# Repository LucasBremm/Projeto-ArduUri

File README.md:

# Projeto ArduUri

## Descrição

Projeto com o objetivo de desenvolver kits robóticos reutilizando lixo eletrônico, sendo esses enviados para escolas, podendo assim desenvolver um aprendizado sobre robótica e programação, juntamente com a conscientização dos riscos ao meio ambiente ocasionados pelo descarte incorreto de componentes eletrônicos.

Atualmente nesse repositório constam:

- Uma placa de circuito que age como Controlador (baseado em Arduino) e uma ponte H para controle de motores

- Duas placas que agem separadamente como a descrita acima

- Moldes em 3D de chassis e suportes para motores, que podem ser impressos com impressora 3D

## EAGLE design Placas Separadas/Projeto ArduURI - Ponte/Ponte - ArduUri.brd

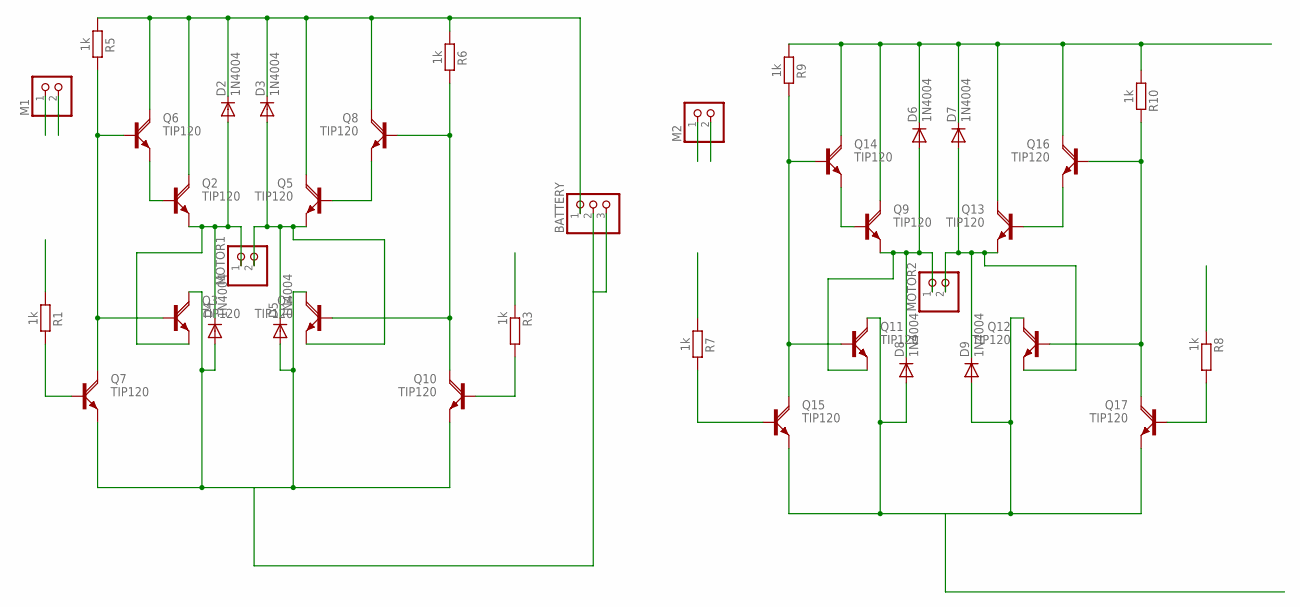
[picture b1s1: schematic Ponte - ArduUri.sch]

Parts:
BATTERY: PINHD-1X3; 1X03
D2, D3, D4, D5, D6, D7, D8, D9: 1N4004; DO41-10
M1, M2: PINHD-1X2; 1X02
MOTOR1, MOTOR2: PINHD-1X2; 1X02
Q2, Q3, Q4, Q5, Q6, Q7, Q8, Q9, Q10, Q11, Q12, Q13, Q14, Q15, Q16, Q17: TIP120; TO220AH
R1, R3, R5, R6, R7, R8, R9, R10: 1k; 0204/7

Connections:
GND: BATTERY.2, BATTERY.3, D4.A, D5.A, D8.A, D9.A, Q3.C, Q4.C, Q7.E, Q10.E, Q11.C, Q12.C, Q15.E, Q17.E
M1-A1: M1.1, R1.1
M1-B1: M1.2, R3.1
M2-A2: M2.1, R7.1
M2-B2: M2.2, R8.1
unnamed: Q5.B, Q8.E
unnamed: Q10.B, R3.2
unnamed: Q7.B, R1.2
unnamed: Q2.B, Q6.E
unnamed: Q9.B, Q14.E
unnamed: Q3.B, Q6.B, Q7.C, R5.2
unnamed: Q4.B, Q8.B, Q10.C, R6.2
unnamed: Q13.B, Q16.E
unnamed: D2.A, D4.C, MOTOR1.1, Q2.E, Q3.E
unnamed: D3.A, D5.C, MOTOR1.2, Q4.E, Q5.E
unnamed: Q17.B, R8.2
unnamed: Q15.B, R7.2
unnamed: Q11.B, Q14.B, Q15.C, R9.2
unnamed: Q12.B, Q16.B, Q17.C, R10.2
unnamed: D6.A, D8.C, MOTOR2.1, Q9.E, Q11.E
unnamed: D7.A, D9.C, MOTOR2.2, Q12.E, Q13.E
VCC-BAT: BATTERY.1, D2.C, D3.C, D6.C, D7.C, Q2.C, Q5.C, Q6.C, Q8.C, Q9.C, Q13.C, Q14.C, Q16.C, R5.1, R6.1, R9.1, R10.1

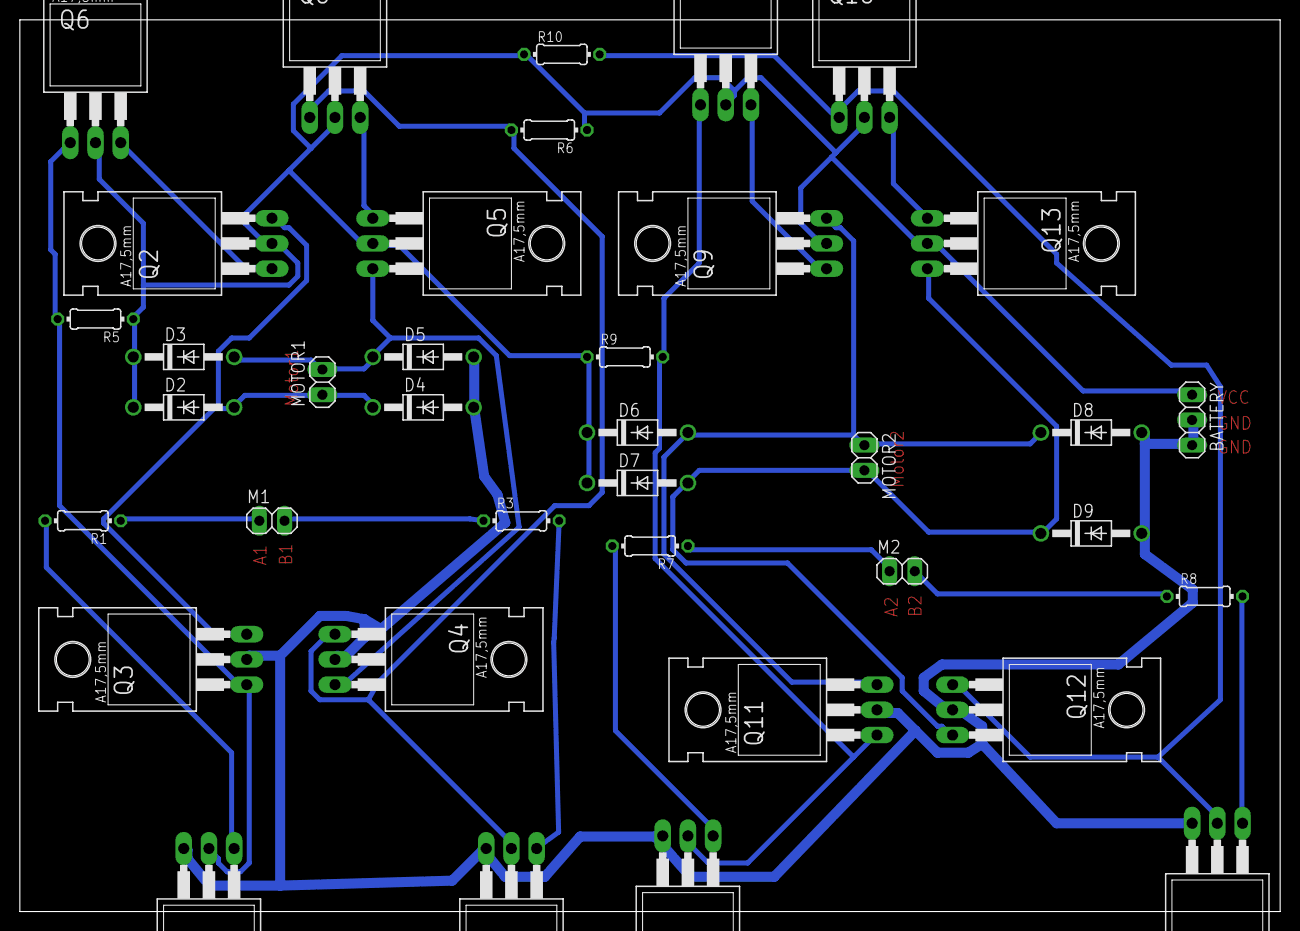
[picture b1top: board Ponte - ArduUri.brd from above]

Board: 2 copper layers, 127.0 x 89.8 mm, 37 parts (0 on the bottom side), 22 nets.

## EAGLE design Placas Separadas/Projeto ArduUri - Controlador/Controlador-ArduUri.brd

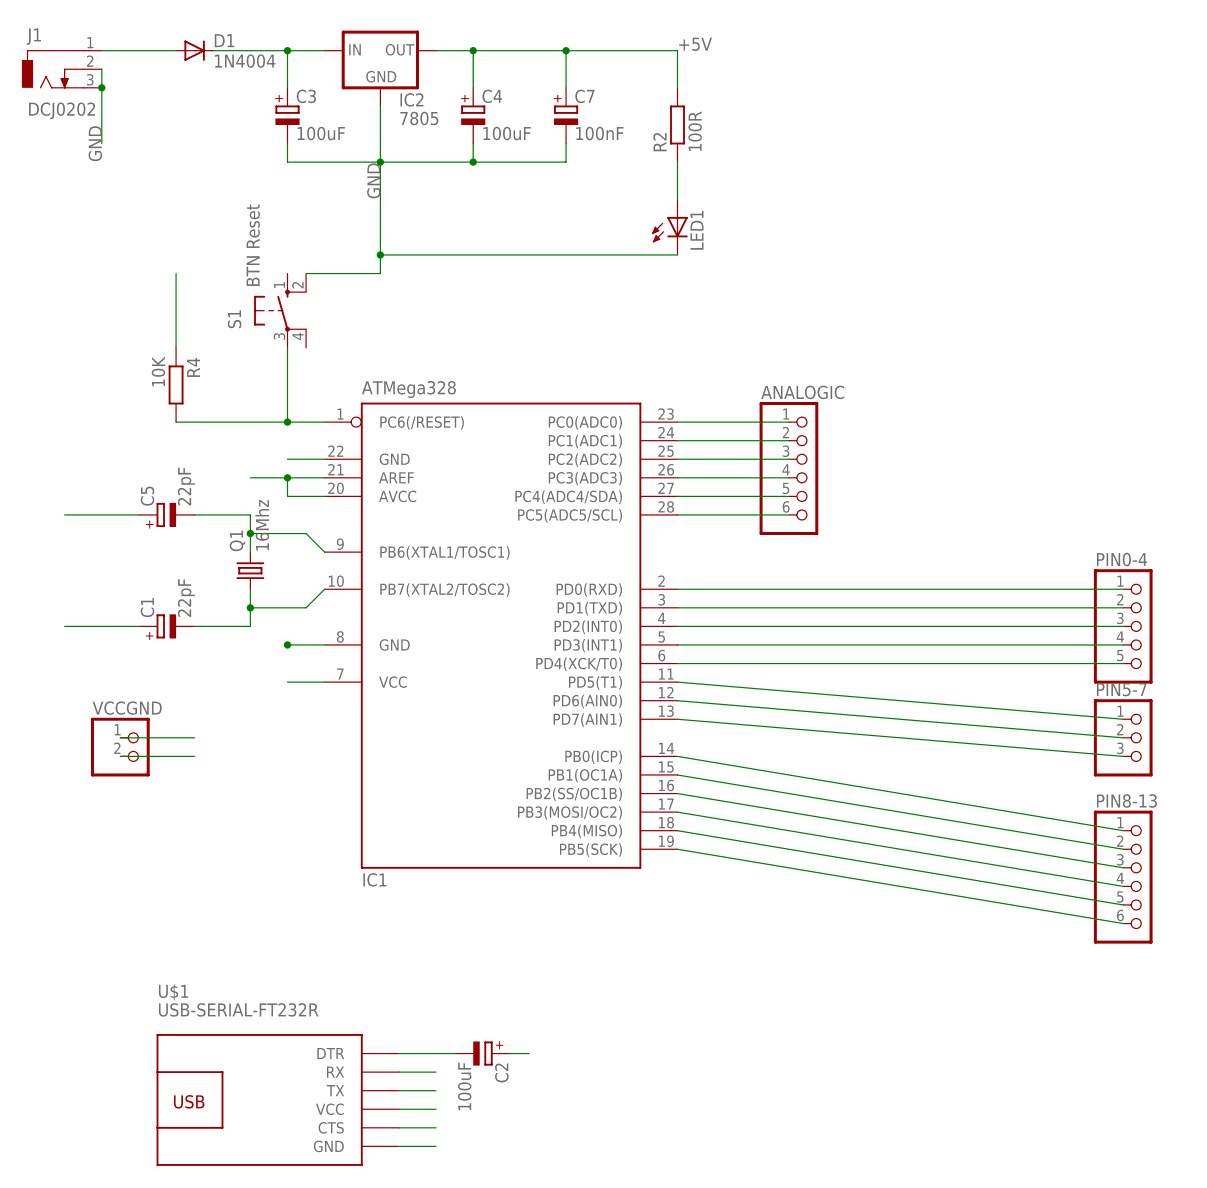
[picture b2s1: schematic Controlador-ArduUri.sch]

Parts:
ANALOGIC: PINHD-1X6; 1X06
C1, C5: 22pF; E2,5-5
C2, C3, C4: 100uF; TAP5-50
C7: 100nF; E2,5-5
D1: 1N4004; DO41-10
IC1: ATMega328; DIL28-3
IC2: 7805; 78XXL
J1: DCJ0202
LED1: LED5MM
PIN0-4: PINHD-1X5; 1X05
PIN5-7: PINHD-1X3; 1X03
PIN8-13: PINHD-1X6; 1X06
Q1: 16Mhz; HC49/S
R2: 100R; 0204/7
R4: 10K; 0204/7
S1: BTN Reset; B3F-10XX
U$1: USB-SERIAL-FT232R
VCCGND: PINHD-1X2; 1X02

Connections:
+5V: C4.+, C7.+, IC1.7 (VCC), IC1.20 (AVCC), IC1.21 (AREF), IC2.OUT, R2.2, R4.1, U$1.4 (VCC), VCCGND.1
DTR: C2.-, U$1.1 (DTR)
GND: C1.+, C3.-, C4.-, C5.+, C7.-, IC1.8 (GND), IC1.22 (GND), IC2.GND, J1.2, J1.3, LED1.K (C), S1.2 (S1), U$1.6 (GND), VCCGND.2
M1-A1: IC1.17 (PB3(MOSI/OC2)), PIN8-13.4
M1-B1: IC1.16 (PB2(SS/OC1B)), PIN8-13.3
M2-A1: IC1.12 (PD6(AIN0)), PIN5-7.2
M2-B1: IC1.11 (PD5(T1)), PIN5-7.1
unnamed: C5.-, IC1.9 (PB6(XTAL1/TOSC1)), Q1.2
unnamed: C1.-, IC1.10 (PB7(XTAL2/TOSC2)), Q1.1
unnamed: D1.A, J1.1
unnamed: C3.+, D1.C, IC2.IN
unnamed: ANALOGIC.1, IC1.23 (PC0(ADC0))
unnamed: ANALOGIC.2, IC1.24 (PC1(ADC1))
unnamed: ANALOGIC.3, IC1.25 (PC2(ADC2))
unnamed: ANALOGIC.4, IC1.26 (PC3(ADC3))
unnamed: ANALOGIC.5, IC1.27 (PC4(ADC4/SDA))
unnamed: ANALOGIC.6, IC1.28 (PC5(ADC5/SCL))
unnamed: IC1.4 (PD2(INT0)), PIN0-4.3
unnamed: IC1.5 (PD3(INT1)), PIN0-4.4
unnamed: IC1.6 (PD4(XCK/T0)), PIN0-4.5
unnamed: IC1.13 (PD7(AIN1)), PIN5-7.3
unnamed: IC1.14 (PB0(ICP)), PIN8-13.1
unnamed: IC1.15 (PB1(OC1A)), PIN8-13.2
unnamed: IC1.18 (PB4(MISO)), PIN8-13.5
unnamed: IC1.19 (PB5(SCK)), PIN8-13.6
unnamed: LED1.A, R2.1
RESET: C2.+, IC1.1 (PC6(/RESET)), R4.2, S1.3
RX: IC1.2 (PD0(RXD)), PIN0-4.1, U$1.3 (TX)
TX: IC1.3 (PD1(TXD)), PIN0-4.2, U$1.2 (RX)

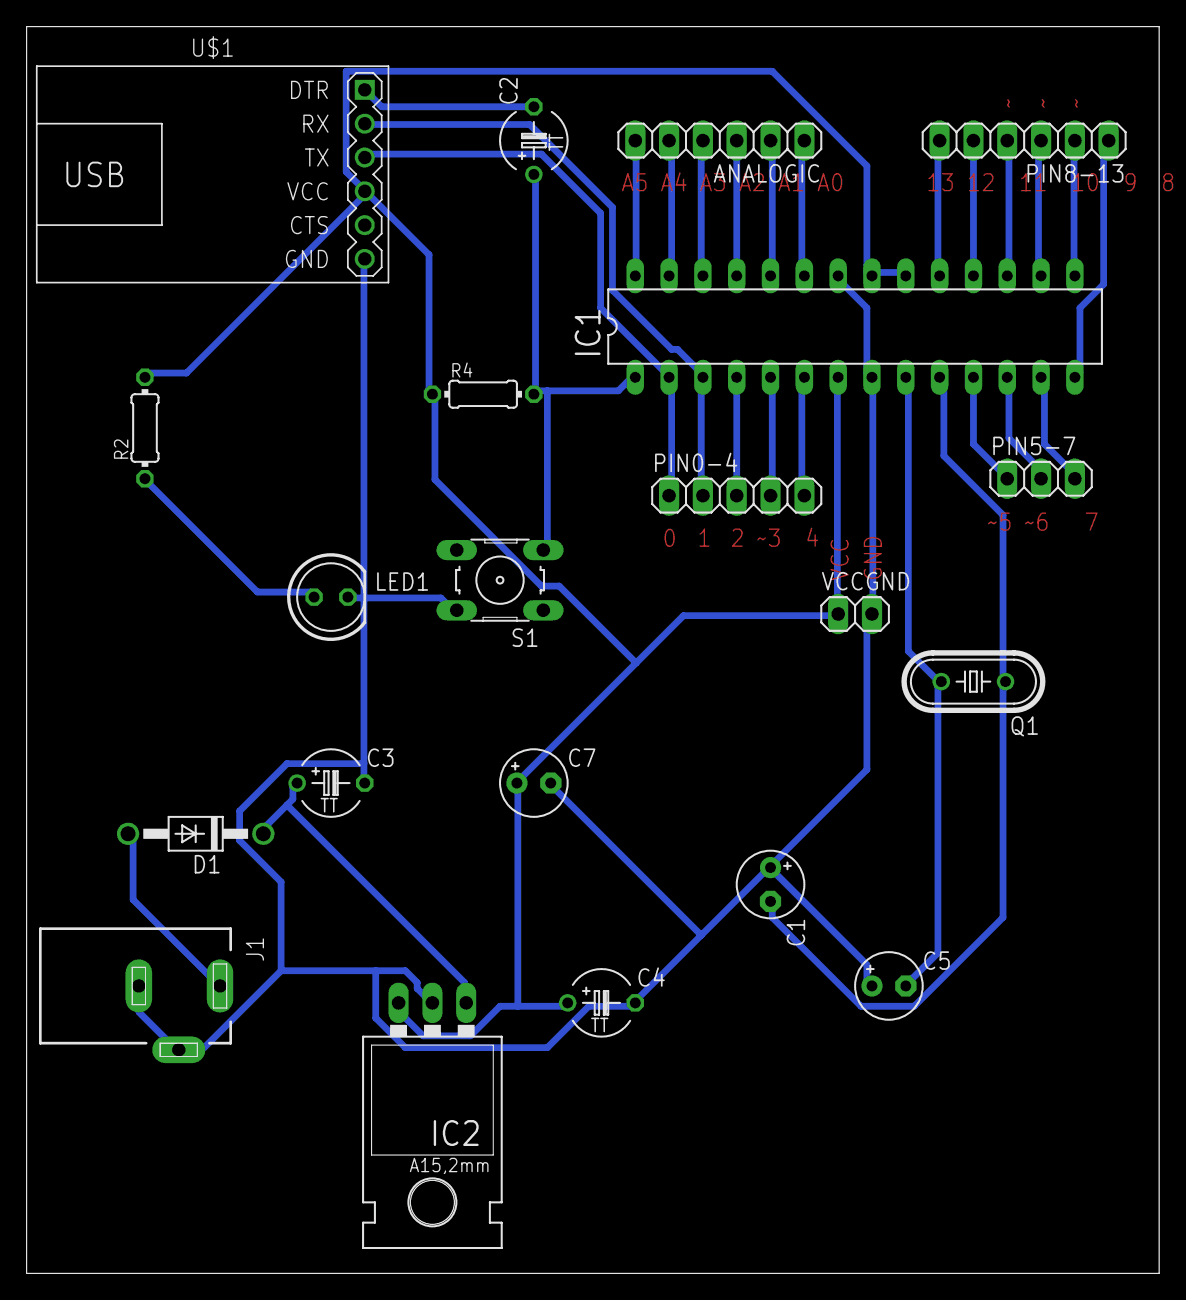
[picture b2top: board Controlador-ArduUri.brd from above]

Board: 2 copper layers, 85.1 x 93.7 mm, 21 parts (0 on the bottom side), 29 nets.

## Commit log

2019-09-13 Primeira versão do projeto

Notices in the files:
parts and their libraries:
diy-modules: Released under the Creative Commons Attribution 4.0 International License: http://creativecommons.org/licenses/by/4.0
